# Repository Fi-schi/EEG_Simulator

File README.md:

# EEG-Simulator

Ein Projektseminar an der Hochschule Wismar zur **Entwicklung eines
EEG-Signalgenerators**. 
Ziel ist es, eine kompakte, intuitive und didaktisch nutzbare Plattform
zur Erzeugung synthetischer EEG-Signale bereitzustellen.

## Features

-   4 analoge Ausgangskanäle für simultane Signalwiedergabe 
-   Steuerung über einen **ESP32-S3 Mikrocontroller** 
-   Hochauflösender DAC (**DAC8412FPZ**) mit 12-Bit Auflösung 
-   Benutzerfreundliche **Weboberfläche** zur Signalverwaltung 
-   Upload eigener Signaldateien über WLAN 
-   Signale im Mikrovoltbereich durch Tiefpassfilter & Spannungsteiler 
-   Keine zusätzliche Softwareinstallation erforderlich (Bedienung im
    Browser)

## Architektur

-   **Hardware**
    -   ESP32-S3 Mikrocontroller (Steuerung, WLAN, Webserver)
    -   DAC8412FPZ (Digital-Analog-Wandler, 4 Kanäle)
    -   TL071CDR Operationsverstärker (aktive Tiefpassfilter)
    -   Spannungsversorgung über USB-C, mit ±5 V und 3,3 V Regulierung
-   **Software**
    -   Frontend: HTML, CSS, JavaScript (Single Page Application)
    -   Backend: ESP32-Firmware in C++ (PlatformIO, ESPAsyncWebServer)
    -   Dateiverwaltung & Signalzuweisung über Webinterface
    -   DAC-Steuerung und Echtzeit-Signalausgabe

## Getting Started

1.  Platine über **USB-C** mit Strom versorgen 
2.  Verbindung mit dem WLAN **EEGsimulator** (Passwort:
    `EEGsimulator2525`) 
3.  Browser öffnen und `192.168.4.1` eingeben 
4.  Über die Weboberfläche:
    -   Signaldateien (`.txt`) hochladen 
    -   Dateien Kanälen zuweisen 
    -   „Verarbeitung anstoßen" und anschließend „Abspielen" klicken

## Dateiformat für Signale

-   Textdateien mit Zahlenwerten (positive/negative Amplituden) 
-   Automatische Skalierung auf den **12-Bit Wertebereich (0--4095)** 
-   Mapping:
    -   Negative Werte → 0--2047 
    -   Positive Werte → 2048--4095

## Hinweise

-   Für stabile Ausgabe eine saubere Stromversorgung sicherstellen 
-   Signale lassen sich per Oszilloskop überwachen 
-   Änderungen an Reihenfolge oder Kanälen erfordern erneute
    Verarbeitung

## Ausblick

-   Verbesserte analoge Filter (z. B. Sallen-Key) 
-   Optimierte Stromversorgung (LDOs oder Akkubetrieb) 
-   Bibliothek vordefinierter EEG-Signalformen (Alpha-/Beta-Wellen
    etc.) 
-   Live-Visualisierung der Signale direkt im Browser

------------------------------------------------------------------------

Entwickelt von **Johannes Fischer** im Rahmen des Projektseminars an
der **Hochschule Wismar**

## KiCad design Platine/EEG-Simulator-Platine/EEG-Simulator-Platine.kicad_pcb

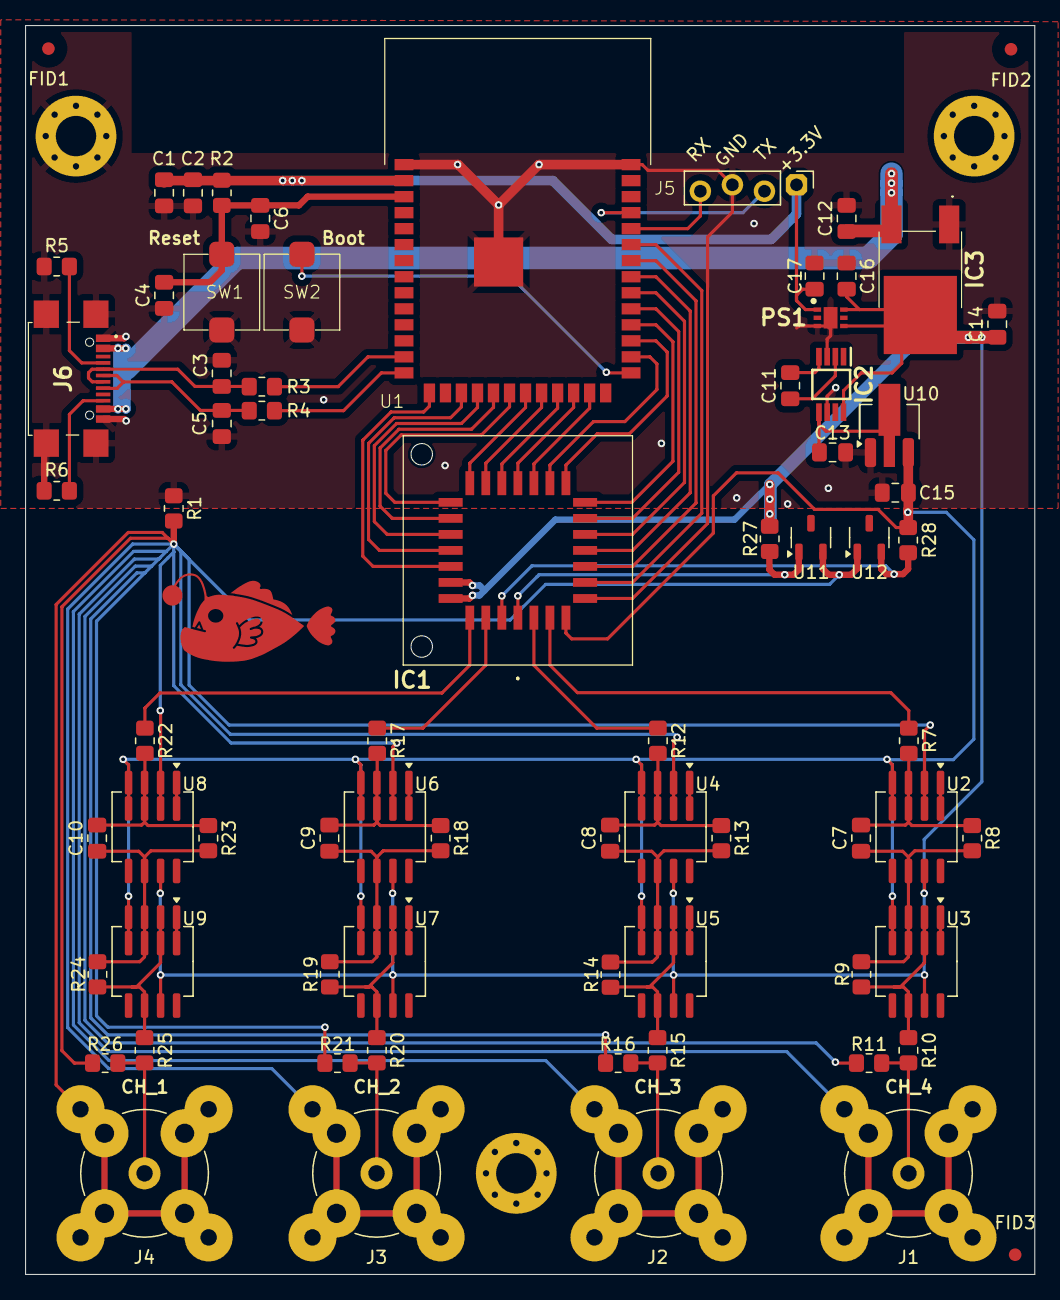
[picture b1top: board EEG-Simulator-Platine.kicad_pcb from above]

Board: 2 copper layers, 80.0 x 99.0 mm, 77 parts (1 on the bottom side), 59 nets.

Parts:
C1: 22µF; C_0805_2012Metric_Pad1.18x1.45mm_HandSolder
C2, C15: 0.1µF; C_0805_2012Metric_Pad1.18x1.45mm_HandSolder
C3, C5: 15pF; C_0805_2012Metric_Pad1.18x1.45mm_HandSolder
C4: 0,1µ; C_0805_2012Metric_Pad1.18x1.45mm_HandSolder
C6, C7, C8, C9, C10: 1µ; C_0805_2012Metric_Pad1.18x1.45mm_HandSolder
C11, C12, C14, C16, C17: 10µF; C_0805_2012Metric_Pad1.18x1.45mm_HandSolder
C13: 0.33µF; C_0805_2012Metric_Pad1.18x1.45mm_HandSolder
FID1, FID2, FID3: Fiducial; Fiducial_1mm_Mask3mm
H1, H2, H3: MountingHole_Pad; MountingHole_3.2mm_M3_Pad_Via
IC1: DAC8412FPZ; 842821B1RKTP
IC2: TL7660CDGKR; SOP65P490X110-8N
IC3: NCV1117DT50RKG
J1, J2, J3, J4: Conn_Coaxial; BNC_THT_Socket
J5: Conn_01x04_Pin; Steckerleiste_1x4_2,54mm
J6: USB4110-GF-A; USB4110GFA
L1: Fischi
L2: HS_Wismar_Corporate_Design
PS1: TLV75733PDRVR; SON65P200X200X80-7N
R1, R9, R14, R19, R24: 0R; R_0805_2012Metric_Pad1.20x1.40mm_HandSolder
R2, R5, R6: 5.1K; R_0805_2012Metric_Pad1.20x1.40mm_HandSolder
R3, R4: 22; R_0805_2012Metric_Pad1.20x1.40mm_HandSolder
R7, R8, R10, R12, R13, R15, R17, R18, R20, R22, R23, R25: 1K; R_0805_2012Metric_Pad1.20x1.40mm_HandSolder
R11, R16, R21, R26: 1; R_0805_2012Metric_Pad1.20x1.40mm_HandSolder
R27, R28: 1k; R_0805_2012Metric_Pad1.20x1.40mm_HandSolder
SW1: Reset; Takt_Schalter_Aliexpress
SW2: Boot; Takt_Schalter_Aliexpress
U1: ESP32-S3-WROOM-1-N16R8
U2, U3, U4, U5, U6, U7, U8, U9: TL071CDR; SOIC-8_4_5.3_combo_P1.27mm
U10: DI79L05UAB; SOT-89-3_Handsoldering
U11, U12: TS4061AILT-1.25; SOT-23-3

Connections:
+3.3V: C1.1, C2.1, C17.1, J5.1, PS1.1 (OUT), R2.1, U1.2 (3V3)
+5V: C14.1, C16.1, IC1.24 (VLOGIC), IC1.25 (VDD), IC2.8 (VCC), IC3.2 (OUTPUT), PS1.4 (EN), PS1.6 (IN), R27.1, U2.7 (V+), U3.7 (V+), U4.7 (V+), U5.7 (V+), U6.7 (V+), U7.7 (V+), U8.7 (V+), U9.7 (V+)
+5V_EX: C12.1, IC3.3 (INPUT), J6.VBUS
-5V: C15.1, IC1.4 (VSS), R28.2, U2.4 (V-), U3.4 (V-), U4.4 (V-), U5.4 (V-), U6.4 (V-), U7.4 (V-), U8.4 (V-), U9.4 (V-), U10.3 (V_out)
/ADD0: IC1.22 (A0), U1.17 (IO9)
/ADD1: IC1.21 (A1), U1.18 (IO10)
/DB0: IC1.8 (DB0_(LSB)), U1.33 (IO40)
/DB1: IC1.9 (DB1), U1.32 (IO39)
/DB2: IC1.10 (DB2), U1.31 (IO38)
/DB3: IC1.11 (DB3), U1.30 (IO37)
/DB4: IC1.12 (DB4), U1.29 (IO36)
/DB5: IC1.13 (DB5), U1.28 (IO35)
/DB6: IC1.14 (DB6), U1.25 (IO48)
/DB7: IC1.15 (DB7), U1.24 (IO47)
/DB8: IC1.16 (DB8), U1.23 (IO21)
/DB9: IC1.17 (DB9), U1.22 (IO14)
/DB10: IC1.18 (DB10), U1.21 (IO13)
/DB11: IC1.19 (DB11_(MSB)), U1.20 (IO12)
/ESP32-S3/EN: C4.2, C6.1, R2.2, SW1.1, U1.3 (EN)
/ESP32-S3/USB_DM: C3.1, J6.A7/B7 (USB_DP), R3.2
/ESP32-S3/USB_DP: C5.1, J6.A6/B6 (USB_DP), R4.2
/Load_Data: IC1.7 (~LDAC), U1.34 (IO41)
/OPV_mit_Tiefpass1/EEG_Out: J2.1 (In), R15.2, R16.1
/OPV_mit_Tiefpass2/EEG_Out: J3.1 (In), R20.2, R21.1
/OPV_mit_Tiefpass3/EEG_Out: J4.1 (In), R25.2, R26.1
/OPV_mit_Tiefpass/EEG_Out: J1.1 (In), R10.2, R11.1
/RST: IC1.6 (~RESET), U1.35 (IO42)
/R/!W: IC1.20 (R/~W), U1.19 (IO11)
/VOUTA: IC1.3 (VOUTA), R7.1
/VOUTB: IC1.2 (VOUTB), R12.1
/VOUTC: IC1.27 (VOUTC), R17.1
/VOUTD: IC1.26 (VOUTD), R22.1
/~CS: IC1.23 (~CS), U1.15 (IO3)
GND: C1.2, C2.2, C3.2, C4.1, C5.2, C6.2, C12.2, C13.2, C14.2, C15.2, C16.2, C17.2, H2.1, IC1.5 (DGND), IC2.3 (GND), IC2.6 (LV), IC3.1 (GND), J5.3, J6.GND, J6.MP, PS1.3 (GND_1), PS1.7 (GND_2), R1.1, R5.1, R6.1, SW1.2, SW2.2, U1.1 (GND), U1.40 (GND), U1.41 (EPAD), U10.1 (GND)
GNDA: J1.2 (Ext), J2.2 (Ext), J3.2 (Ext), J4.2 (Ext), R1.2, R11.2, R16.2, R21.2, R26.2, U2.2 (-), U4.2 (-), U6.2 (-), U8.2 (-), U11.2 (A), U12.1 (K)
unnamed: C11.1, IC2.2 (CAP+)
unnamed: C11.2, IC2.4 (CAP-)
unnamed: C13.1, IC2.5 (VOUT), U10.2 (V_in)
unnamed: J5.2, U1.37 (TXD0)
unnamed: J5.4, U1.36 (RXD0)
unnamed: J6.A5 (CC1), R5.2
unnamed: J6.B5 (CC2), R6.2
unnamed: SW2.1, U1.27 (IO0)
unnamed: R3.1, U1.13 (IO19)
unnamed: R4.1, U1.14 (IO20)
unnamed: C7.2, R7.2, R8.1, U2.3 (+)
unnamed: C7.1, R8.2, R9.1, U2.6, U3.3 (+)
unnamed: R9.2, R10.1, U3.2 (-), U3.6
unnamed: C8.2, R12.2, R13.1, U4.3 (+)
unnamed: C8.1, R13.2, R14.1, U4.6, U5.3 (+)
unnamed: R14.2, R15.1, U5.2 (-), U5.6
unnamed: C9.2, R17.2, R18.1, U6.3 (+)
unnamed: C9.1, R18.2, R19.1, U6.6, U7.3 (+)
unnamed: R19.2, R20.1, U7.2 (-), U7.6
unnamed: C10.2, R22.2, R23.1, U8.3 (+)
unnamed: C10.1, R23.2, R24.1, U8.6, U9.3 (+)
unnamed: R24.2, R25.1, U9.2 (-), U9.6
V_REFH: IC1.1 (VREFH), R27.2, U11.1 (K)
V_REFL: IC1.28 (VREFL), R28.1, U12.2 (A)

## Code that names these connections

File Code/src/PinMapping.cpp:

#include <Arduino.h>
#include "PinMapping.hpp"

void initPinModes() {
  // Datenleitungen
  pinMode(DB0, OUTPUT);
  pinMode(DB1, OUTPUT);
  pinMode(DB2, OUTPUT);
  pinMode(DB3, OUTPUT);
  pinMode(DB4, OUTPUT);
  pinMode(DB5, OUTPUT);
  pinMode(DB6, OUTPUT);
  pinMode(DB7, OUTPUT);
  pinMode(DB8, OUTPUT);
  pinMode(DB9, OUTPUT);
  pinMode(DB10, OUTPUT);
  pinMode(DB11, OUTPUT);

  // Adressleitungen
  pinMode(ADD0, OUTPUT);
  pinMode(ADD1, OUTPUT);

  // Steuerleitungen
  pinMode(RST, OUTPUT);
  pinMode(Load_Data, OUTPUT);
  pinMode(R_W, OUTPUT);
  pinMode(CS, OUTPUT);
  digitalWrite(CS, HIGH); // Inaktiv setzen
  
}

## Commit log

2025-09-17 Final Push
2025-09-17 Organisation
